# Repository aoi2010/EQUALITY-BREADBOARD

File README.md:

# Equality Breadboard
A breadboard with both male and female header pins.

### Inspiration

I searched in google about Male Breadboards but no results came up. I thought why only breadboards with female header pins are available in the market. So I decided to make a breadboard with both male and female header pins. And, here we are! A breadboard with both male and female header pins. I hope this project will be useful for everyone who wants to use a breadboard with both male and female header pins. lol

### Challenges

Finding 1x40 header pins was a challenge as they are mostly out of stock in India.

### How To Use This
- STEP 1: Buy all the things listed in the BOM, and order the PCB.
- STEP 2: Solder the header pins to the PCB.
- STEP 3: Voila! You have your breadboard ready!
- STEP 4: Do Anything With It and have fun!
Thank You! Also Please give a star to this poor fellow if you like the project. Thank You Again!

### Specifications

BOM (from `BOM.csv`):

| Name | Qty | Purpose | Total Cost (USD) | Link | Distributor |
|---|---:|---|---:|---|---|
| 2.54mm 40x1 Male Blue Straight Burg Strips (Pack of 5) | 7 | BREADBOARD PINS | $1.70 | [Buy](https://roboticsdna.in/product/2-54mm-40x1-male-blue-straight-burg-strips-pack-of-5/) | Robotics DNA |
| 40x2 Pin 2.54mm Pitch Male Berg Strip | 3 | BREADBOARD PINS | $0.40 | [Buy](https://robocraze.com/products/40x2-pin-2-54mm-pitch-male-berg-strip?variant=43046631801056) | Robocraze |
| 40x2 Female Berg Strip | 1 | BREADBOARD PINS | $0.20 | [Buy](https://robocraze.com/products/40x2-female-berg-strip?variant=40192365887641) | Robocraze |
| 40x1 Female Berg Strip | 11 | BREADBOARD PINS | $1.10 | [Buy](https://robocraze.com/products/40x1-female-berg-strip?variant=40192367689881) | Robocraze |
| PCB | 5 | PCB | $12.46 | N/A | JLCPCB |
| TAX | 1 | TAX | $1.00 | N/A | Indian Govt. |
| SHIPPING | 2 | SHIPPING | $1.33 | N/A | Robocraze & Robotics DNA |

Others:
- PCB Gerber Files

Schematic | PCB Layout |
:-------------------------:|:-------------------------:|
 |  |

PCB Top | PCB Back | PCB Side |
:-------------------------:|:-------------------------:|:-------------------------:|
 |  |  |

### Notes
You can also switch the whole breadboard to male header pins if you want. Just solder the male header pins to the PCB instead of the female header pins. But, I have designed the PCB in such a way that you can easily switch between male and female header pins.

Thank You for Understanding.
<div align="center">

## Thanks For Reading! Also leave a star if you like the project! ⭐

</div>

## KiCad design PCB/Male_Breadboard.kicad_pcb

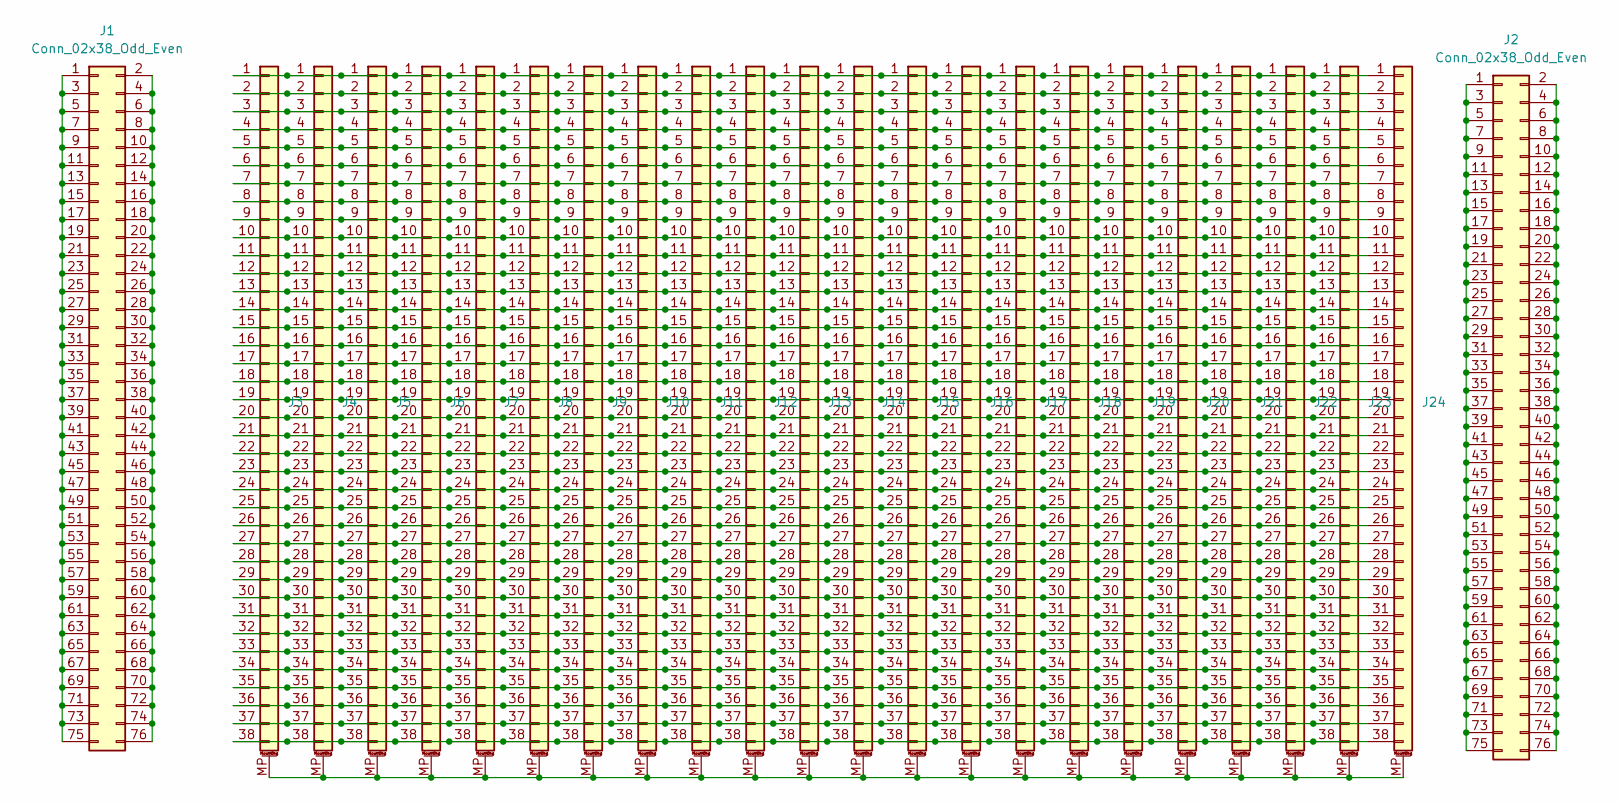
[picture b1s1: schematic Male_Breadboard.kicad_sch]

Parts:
J1: Conn_02x38_Odd_Even; PinHeader_2x38_P2.54mm_Vertical
J2: Conn_02x38_Odd_Even; PinSocket_2x38_P2.54mm_Vertical
J3, J5, J7, J9, J11, J13, J15, J17, J19, J21, J23: Conn_01x38_MountingPin; PinSocket_1x38_P2.54mm_Vertical
J4, J6, J8, J10, J12, J14, J16, J18, J20, J22, J24: Conn_01x38_MountingPin; PinHeader_1x38_P2.54mm_Vertical

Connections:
unnamed: J1.1, J1.3, J1.5, J1.7, J1.9, J1.11, J1.13, J1.15, J1.17, J1.19, J1.21, J1.23, J1.25, J1.27, J1.29, J1.31, J1.33, J1.35, J1.37, J1.39, J1.41, J1.43, J1.45, J1.47, J1.49, J1.51, J1.53, J1.55, J1.57, J1.59, J1.61, J1.63, J1.65, J1.67, J1.69, J1.71, J1.73, J1.75
unnamed: J1.2, J1.4, J1.6, J1.8, J1.10, J1.12, J1.14, J1.16, J1.18, J1.20, J1.22, J1.24, J1.26, J1.28, J1.30, J1.32, J1.34, J1.36, J1.38, J1.40, J1.42, J1.44, J1.46, J1.48, J1.50, J1.52, J1.54, J1.56, J1.58, J1.60, J1.62, J1.64, J1.66, J1.68, J1.70, J1.72, J1.74, J1.76
unnamed: J2.1, J2.3, J2.5, J2.7, J2.9, J2.11, J2.13, J2.15, J2.17, J2.19, J2.21, J2.23, J2.25, J2.27, J2.29, J2.31, J2.33, J2.35, J2.37, J2.39, J2.41, J2.43, J2.45, J2.47, J2.49, J2.51, J2.53, J2.55, J2.57, J2.59, J2.61, J2.63, J2.65, J2.67, J2.69, J2.71, J2.73, J2.75
unnamed: J2.2, J2.4, J2.6, J2.8, J2.10, J2.12, J2.14, J2.16, J2.18, J2.20, J2.22, J2.24, J2.26, J2.28, J2.30, J2.32, J2.34, J2.36, J2.38, J2.40, J2.42, J2.44, J2.46, J2.48, J2.50, J2.52, J2.54, J2.56, J2.58, J2.60, J2.62, J2.64, J2.66, J2.68, J2.70, J2.72, J2.74, J2.76
unnamed: J3.1, J4.1, J5.1, J6.1, J7.1, J8.1, J9.1, J10.1, J11.1, J12.1, J13.1, J14.1, J15.1, J16.1, J17.1, J18.1, J19.1, J20.1, J21.1, J22.1, J23.1, J24.1
unnamed: J3.2, J4.2, J5.2, J6.2, J7.2, J8.2, J9.2, J10.2, J11.2, J12.2, J13.2, J14.2, J15.2, J16.2, J17.2, J18.2, J19.2, J20.2, J21.2, J22.2, J23.2, J24.2
unnamed: J3.3, J4.3, J5.3, J6.3, J7.3, J8.3, J9.3, J10.3, J11.3, J12.3, J13.3, J14.3, J15.3, J16.3, J17.3, J18.3, J19.3, J20.3, J21.3, J22.3, J23.3, J24.3
unnamed: J3.4, J4.4, J5.4, J6.4, J7.4, J8.4, J9.4, J10.4, J11.4, J12.4, J13.4, J14.4, J15.4, J16.4, J17.4, J18.4, J19.4, J20.4, J21.4, J22.4, J23.4, J24.4
unnamed: J3.5, J4.5, J5.5, J6.5, J7.5, J8.5, J9.5, J10.5, J11.5, J12.5, J13.5, J14.5, J15.5, J16.5, J17.5, J18.5, J19.5, J20.5, J21.5, J22.5, J23.5, J24.5
unnamed: J3.6, J4.6, J5.6, J6.6, J7.6, J8.6, J9.6, J10.6, J11.6, J12.6, J13.6, J14.6, J15.6, J16.6, J17.6, J18.6, J19.6, J20.6, J21.6, J22.6, J23.6, J24.6
unnamed: J3.7, J4.7, J5.7, J6.7, J7.7, J8.7, J9.7, J10.7, J11.7, J12.7, J13.7, J14.7, J15.7, J16.7, J17.7, J18.7, J19.7, J20.7, J21.7, J22.7, J23.7, J24.7
unnamed: J3.8, J4.8, J5.8, J6.8, J7.8, J8.8, J9.8, J10.8, J11.8, J12.8, J13.8, J14.8, J15.8, J16.8, J17.8, J18.8, J19.8, J20.8, J21.8, J22.8, J23.8, J24.8
unnamed: J3.9, J4.9, J5.9, J6.9, J7.9, J8.9, J9.9, J10.9, J11.9, J12.9, J13.9, J14.9, J15.9, J16.9, J17.9, J18.9, J19.9, J20.9, J21.9, J22.9, J23.9, J24.9
unnamed: J3.10, J4.10, J5.10, J6.10, J7.10, J8.10, J9.10, J10.10, J11.10, J12.10, J13.10, J14.10, J15.10, J16.10, J17.10, J18.10, J19.10, J20.10, J21.10, J22.10, J23.10, J24.10
unnamed: J3.11, J4.11, J5.11, J6.11, J7.11, J8.11, J9.11, J10.11, J11.11, J12.11, J13.11, J14.11, J15.11, J16.11, J17.11, J18.11, J19.11, J20.11, J21.11, J22.11, J23.11, J24.11
unnamed: J3.12, J4.12, J5.12, J6.12, J7.12, J8.12, J9.12, J10.12, J11.12, J12.12, J13.12, J14.12, J15.12, J16.12, J17.12, J18.12, J19.12, J20.12, J21.12, J22.12, J23.12, J24.12
unnamed: J3.13, J4.13, J5.13, J6.13, J7.13, J8.13, J9.13, J10.13, J11.13, J12.13, J13.13, J14.13, J15.13, J16.13, J17.13, J18.13, J19.13, J20.13, J21.13, J22.13, J23.13, J24.13
unnamed: J3.14, J4.14, J5.14, J6.14, J7.14, J8.14, J9.14, J10.14, J11.14, J12.14, J13.14, J14.14, J15.14, J16.14, J17.14, J18.14, J19.14, J20.14, J21.14, J22.14, J23.14, J24.14
unnamed: J3.15, J4.15, J5.15, J6.15, J7.15, J8.15, J9.15, J10.15, J11.15, J12.15, J13.15, J14.15, J15.15, J16.15, J17.15, J18.15, J19.15, J20.15, J21.15, J22.15, J23.15, J24.15
unnamed: J3.16, J4.16, J5.16, J6.16, J7.16, J8.16, J9.16, J10.16, J11.16, J12.16, J13.16, J14.16, J15.16, J16.16, J17.16, J18.16, J19.16, J20.16, J21.16, J22.16, J23.16, J24.16
unnamed: J3.17, J4.17, J5.17, J6.17, J7.17, J8.17, J9.17, J10.17, J11.17, J12.17, J13.17, J14.17, J15.17, J16.17, J17.17, J18.17, J19.17, J20.17, J21.17, J22.17, J23.17, J24.17
unnamed: J3.18, J4.18, J5.18, J6.18, J7.18, J8.18, J9.18, J10.18, J11.18, J12.18, J13.18, J14.18, J15.18, J16.18, J17.18, J18.18, J19.18, J20.18, J21.18, J22.18, J23.18, J24.18
unnamed: J3.19, J4.19, J5.19, J6.19, J7.19, J8.19, J9.19, J10.19, J11.19, J12.19, J13.19, J14.19, J15.19, J16.19, J17.19, J18.19, J19.19, J20.19, J21.19, J22.19, J23.19, J24.19
unnamed: J3.20, J4.20, J5.20, J6.20, J7.20, J8.20, J9.20, J10.20, J11.20, J12.20, J13.20, J14.20, J15.20, J16.20, J17.20, J18.20, J19.20, J20.20, J21.20, J22.20, J23.20, J24.20
unnamed: J3.21, J4.21, J5.21, J6.21, J7.21, J8.21, J9.21, J10.21, J11.21, J12.21, J13.21, J14.21, J15.21, J16.21, J17.21, J18.21, J19.21, J20.21, J21.21, J22.21, J23.21, J24.21
unnamed: J3.22, J4.22, J5.22, J6.22, J7.22, J8.22, J9.22, J10.22, J11.22, J12.22, J13.22, J14.22, J15.22, J16.22, J17.22, J18.22, J19.22, J20.22, J21.22, J22.22, J23.22, J24.22
unnamed: J3.23, J4.23, J5.23, J6.23, J7.23, J8.23, J9.23, J10.23, J11.23, J12.23, J13.23, J14.23, J15.23, J16.23, J17.23, J18.23, J19.23, J20.23, J21.23, J22.23, J23.23, J24.23
unnamed: J3.24, J4.24, J5.24, J6.24, J7.24, J8.24, J9.24, J10.24, J11.24, J12.24, J13.24, J14.24, J15.24, J16.24, J17.24, J18.24, J19.24, J20.24, J21.24, J22.24, J23.24, J24.24
unnamed: J3.25, J4.25, J5.25, J6.25, J7.25, J8.25, J9.25, J10.25, J11.25, J12.25, J13.25, J14.25, J15.25, J16.25, J17.25, J18.25, J19.25, J20.25, J21.25, J22.25, J23.25, J24.25
unnamed: J3.26, J4.26, J5.26, J6.26, J7.26, J8.26, J9.26, J10.26, J11.26, J12.26, J13.26, J14.26, J15.26, J16.26, J17.26, J18.26, J19.26, J20.26, J21.26, J22.26, J23.26, J24.26
unnamed: J3.27, J4.27, J5.27, J6.27, J7.27, J8.27, J9.27, J10.27, J11.27, J12.27, J13.27, J14.27, J15.27, J16.27, J17.27, J18.27, J19.27, J20.27, J21.27, J22.27, J23.27, J24.27
unnamed: J3.28, J4.28, J5.28, J6.28, J7.28, J8.28, J9.28, J10.28, J11.28, J12.28, J13.28, J14.28, J15.28, J16.28, J17.28, J18.28, J19.28, J20.28, J21.28, J22.28, J23.28, J24.28
unnamed: J3.29, J4.29, J5.29, J6.29, J7.29, J8.29, J9.29, J10.29, J11.29, J12.29, J13.29, J14.29, J15.29, J16.29, J17.29, J18.29, J19.29, J20.29, J21.29, J22.29, J23.29, J24.29
unnamed: J3.30, J4.30, J5.30, J6.30, J7.30, J8.30, J9.30, J10.30, J11.30, J12.30, J13.30, J14.30, J15.30, J16.30, J17.30, J18.30, J19.30, J20.30, J21.30, J22.30, J23.30, J24.30
unnamed: J3.31, J4.31, J5.31, J6.31, J7.31, J8.31, J9.31, J10.31, J11.31, J12.31, J13.31, J14.31, J15.31, J16.31, J17.31, J18.31, J19.31, J20.31, J21.31, J22.31, J23.31, J24.31
unnamed: J3.32, J4.32, J5.32, J6.32, J7.32, J8.32, J9.32, J10.32, J11.32, J12.32, J13.32, J14.32, J15.32, J16.32, J17.32, J18.32, J19.32, J20.32, J21.32, J22.32, J23.32, J24.32
unnamed: J3.33, J4.33, J5.33, J6.33, J7.33, J8.33, J9.33, J10.33, J11.33, J12.33, J13.33, J14.33, J15.33, J16.33, J17.33, J18.33, J19.33, J20.33, J21.33, J22.33, J23.33, J24.33
unnamed: J3.34, J4.34, J5.34, J6.34, J7.34, J8.34, J9.34, J10.34, J11.34, J12.34, J13.34, J14.34, J15.34, J16.34, J17.34, J18.34, J19.34, J20.34, J21.34, J22.34, J23.34, J24.34
unnamed: J3.35, J4.35, J5.35, J6.35, J7.35, J8.35, J9.35, J10.35, J11.35, J12.35, J13.35, J14.35, J15.35, J16.35, J17.35, J18.35, J19.35, J20.35, J21.35, J22.35, J23.35, J24.35
unnamed: J3.36, J4.36, J5.36, J6.36, J7.36, J8.36, J9.36, J10.36, J11.36, J12.36, J13.36, J14.36, J15.36, J16.36, J17.36, J18.36, J19.36, J20.36, J21.36, J22.36, J23.36, J24.36
unnamed: J3.37, J4.37, J5.37, J6.37, J7.37, J8.37, J9.37, J10.37, J11.37, J12.37, J13.37, J14.37, J15.37, J16.37, J17.37, J18.37, J19.37, J20.37, J21.37, J22.37, J23.37, J24.37
unnamed: J3.38, J4.38, J5.38, J6.38, J7.38, J8.38, J9.38, J10.38, J11.38, J12.38, J13.38, J14.38, J15.38, J16.38, J17.38, J18.38, J19.38, J20.38, J21.38, J22.38, J23.38, J24.38

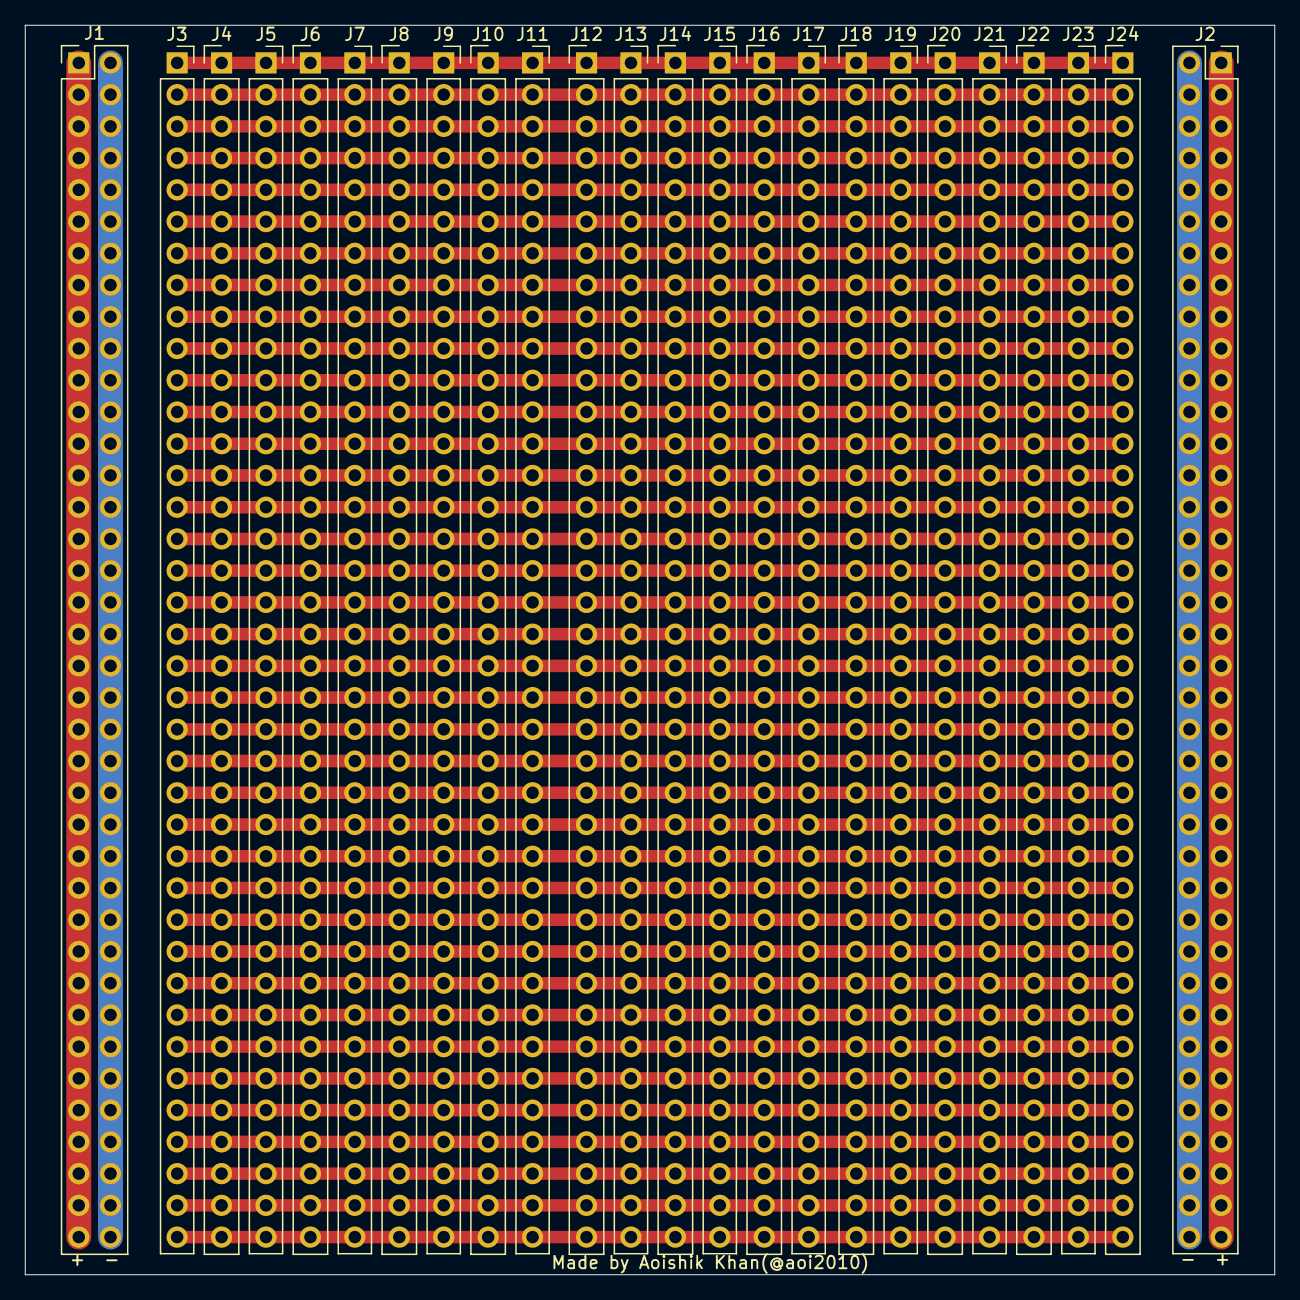
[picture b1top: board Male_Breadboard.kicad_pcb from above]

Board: 2 copper layers, 100.0 x 100.0 mm, 24 parts (0 on the bottom side), 42 nets.

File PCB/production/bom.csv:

Designator,Footprint,Quantity,Value,LCSC Part #
J1,PinHeader_2x38_P2.54mm_Vertical,1,Conn_02x38_Odd_Even,
"J10, J12, J14, J16, J18, J20, J22, J24, J4, J6, J8",PinHeader_1x38_P2.54mm_Vertical,11,Conn_01x38_MountingPin,
"J11, J13, J15, J17, J19, J21, J23, J3, J5, J7, J9",PinSocket_1x38_P2.54mm_Vertical,11,Conn_01x38_MountingPin,
J2,PinSocket_2x38_P2.54mm_Vertical,1,Conn_02x38_Odd_Even,

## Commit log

2026-05-16 Add Kicad files and Add Images and Add README.md
2026-05-17 Update the Gerber files
    Replace the Gerber files with an updated version.
2026-05-17 Add PCB production BOM/positions and track CSVs
    Stop ignoring CSVs and add BOM/placement files for production. Removed "*.csv" from .gitignore so BOMs are tracked. Added top-level BOM.csv listing parts, quantities, costs and suppliers, and added P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
